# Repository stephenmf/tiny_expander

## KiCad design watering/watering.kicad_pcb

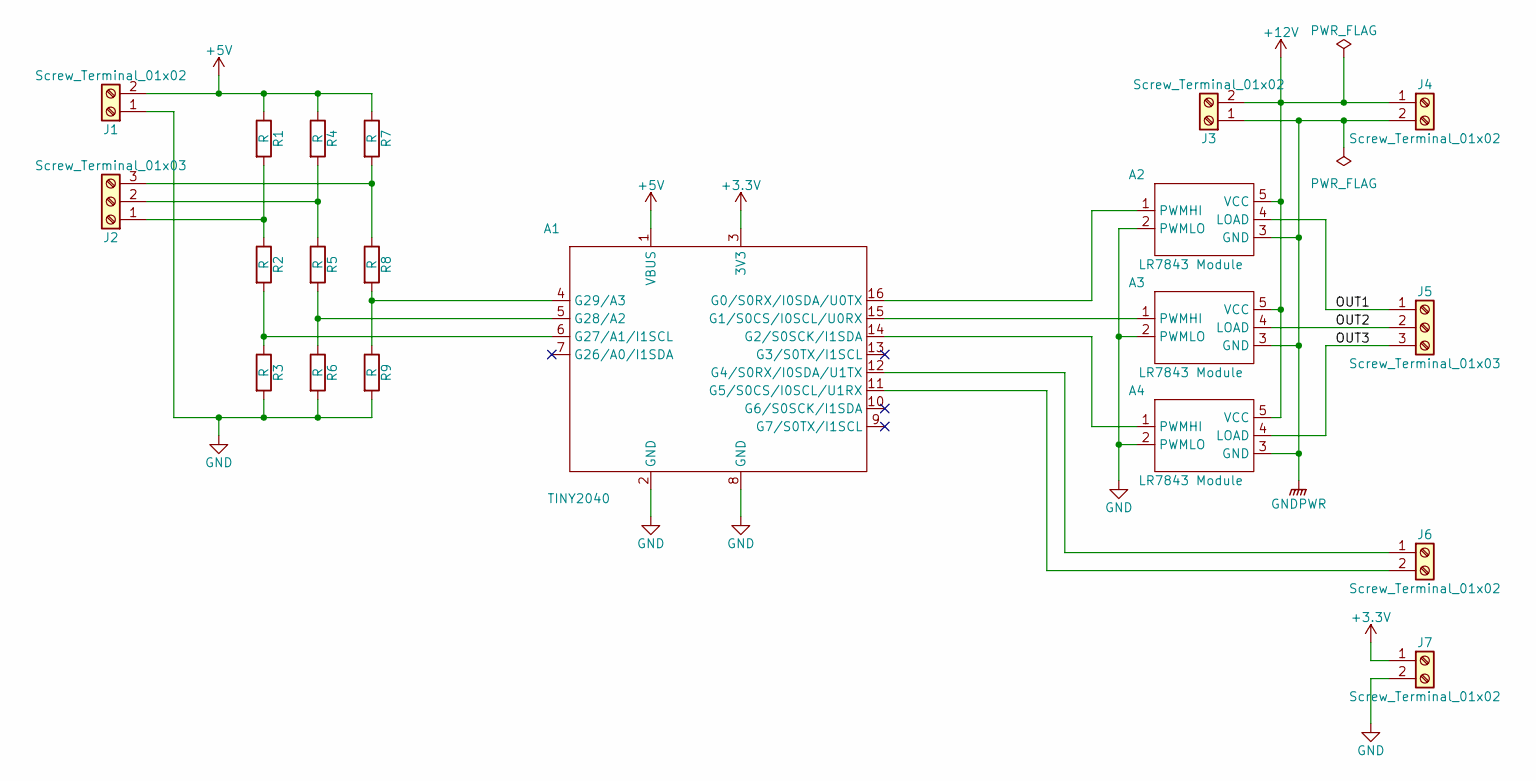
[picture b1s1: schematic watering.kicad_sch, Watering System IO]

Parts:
A1: TINY2040; Tiny2040
A2, A3, A4: LR7843 Module; CMLR7843
J1, J3, J4, J6, J7: Screw_Terminal_01x02; TerminalBlock_Phoenix_MKDS-1,5-2_1x02_P5.00mm_Horizontal
J2, J5: Screw_Terminal_01x03; TerminalBlock_Phoenix_MKDS-1,5-3_1x03_P5.00mm_Horizontal
R1, R2, R3, R4, R5, R6, R7, R8, R9: R; R_Axial_DIN0207_L6.3mm_D2.5mm_P10.16mm_Horizontal

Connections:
+3.3V: A1.3 (3V3), J7.1
+5V: A1.1 (VBUS), J1.2, R1.1, R4.1, R7.1
+12V: A2.5 (VCC), A3.5 (VCC), A4.5 (VCC), J3.2, J4.1
/OUT1: A2.4 (LOAD), J5.1
/OUT2: A3.4 (LOAD), J5.2
/OUT3: A4.4 (LOAD), J5.3
GND: A1.2 (GND), A1.8 (GND), A2.2 (PWMLO), A3.2 (PWMLO), A4.2 (PWMLO), J1.1, J7.2, R3.2, R6.2, R9.2
GNDPWR: A2.3 (GND), A3.3 (GND), A4.3 (GND), J3.1, J4.2
unnamed: A1.16 (G0/S0RX/I0SDA/U0TX), A2.1 (PWMHI)
unnamed: A1.15 (G1/S0CS/I0SCL/U0RX), A3.1 (PWMHI)
unnamed: A1.14 (G2/S0SCK/I1SDA), A4.1 (PWMHI)
unnamed: A1.12 (G4/S0RX/I0SDA/U1TX), J6.1
unnamed: A1.11 (G5/S0CS/I0SCL/U1RX), J6.2
unnamed: A1.6 (G27/A2/I1SCL), R2.2, R3.1
unnamed: A1.5 (G28/A2), R5.2, R6.1
unnamed: A1.4 (G29/A3), R8.2, R9.1
unnamed: J2.1, R1.2, R2.1
unnamed: J2.2, R4.2, R5.1
unnamed: J2.3, R7.2, R8.1

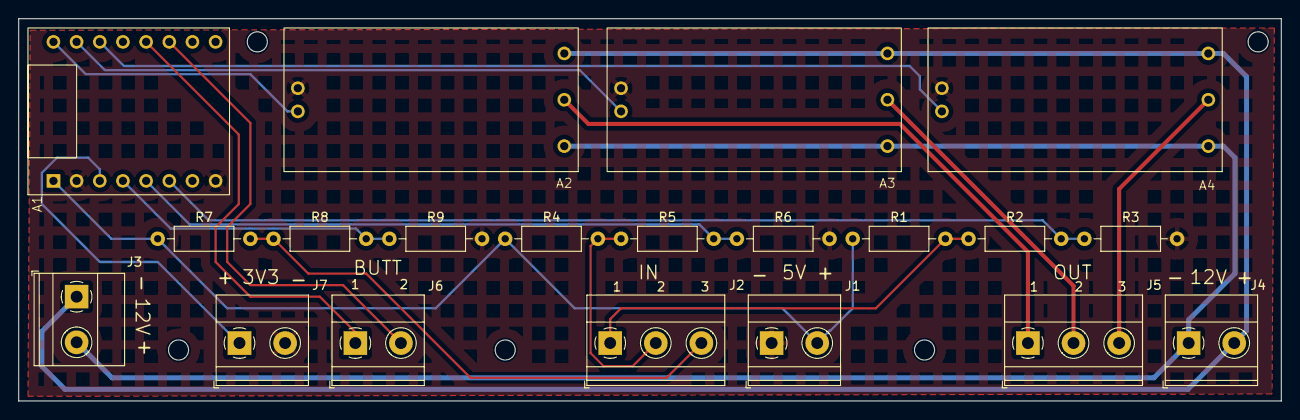
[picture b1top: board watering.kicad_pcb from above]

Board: 2 copper layers, 138.4 x 41.9 mm, 20 parts (0 on the bottom side), 19 nets.

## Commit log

2023-04-02 Remove unused defines.
2023-04-02 Change target
2023-04-02 Change usb product string.
2023-04-02 Update app and simplify parser.
2023-04-25 Add schematic and pcb
2023-04-28 Update debug to use raspberrypi pi debug probe.
2023-04-28 Add RGB led.
2023-04-30 Use templates for io.
2023-05-01 Build in ubuntu
2023-05-06 Add frequency measuring.
2023-05-06 Add flow sensor.
2023-05-07 Update the tiny2040 symbol.
2023-05-08 Use leds as state indicator.
2023-05-08 Chnge connected to white.
2023-05-08 Fix status response json format.
2024-08-05 Update to use pico vscode extension.
2024-08-12 Upgrade sdk to V2.0.0
2025-02-14 Add more sensors re-organise pins
2025-02-14 Change connected indicator to all off.
2025-02-16 Update files to latest kicad version.
2025-02-16 Drive rgb led using pwm.
2025-02-17 Update binary information.
2025-02-17 Restore use of pico_stdlib.
2025-02-19 Swap pins for moisture and flow.
2025-04-16 Updated Kicad to latest version.
2025-04-16 Use CLI rather vscode integration to build.
2025-04-16 Finished update to KiCad 9.0
2025-04-16 Upadte debug to reflect CLI usage within vscode.
